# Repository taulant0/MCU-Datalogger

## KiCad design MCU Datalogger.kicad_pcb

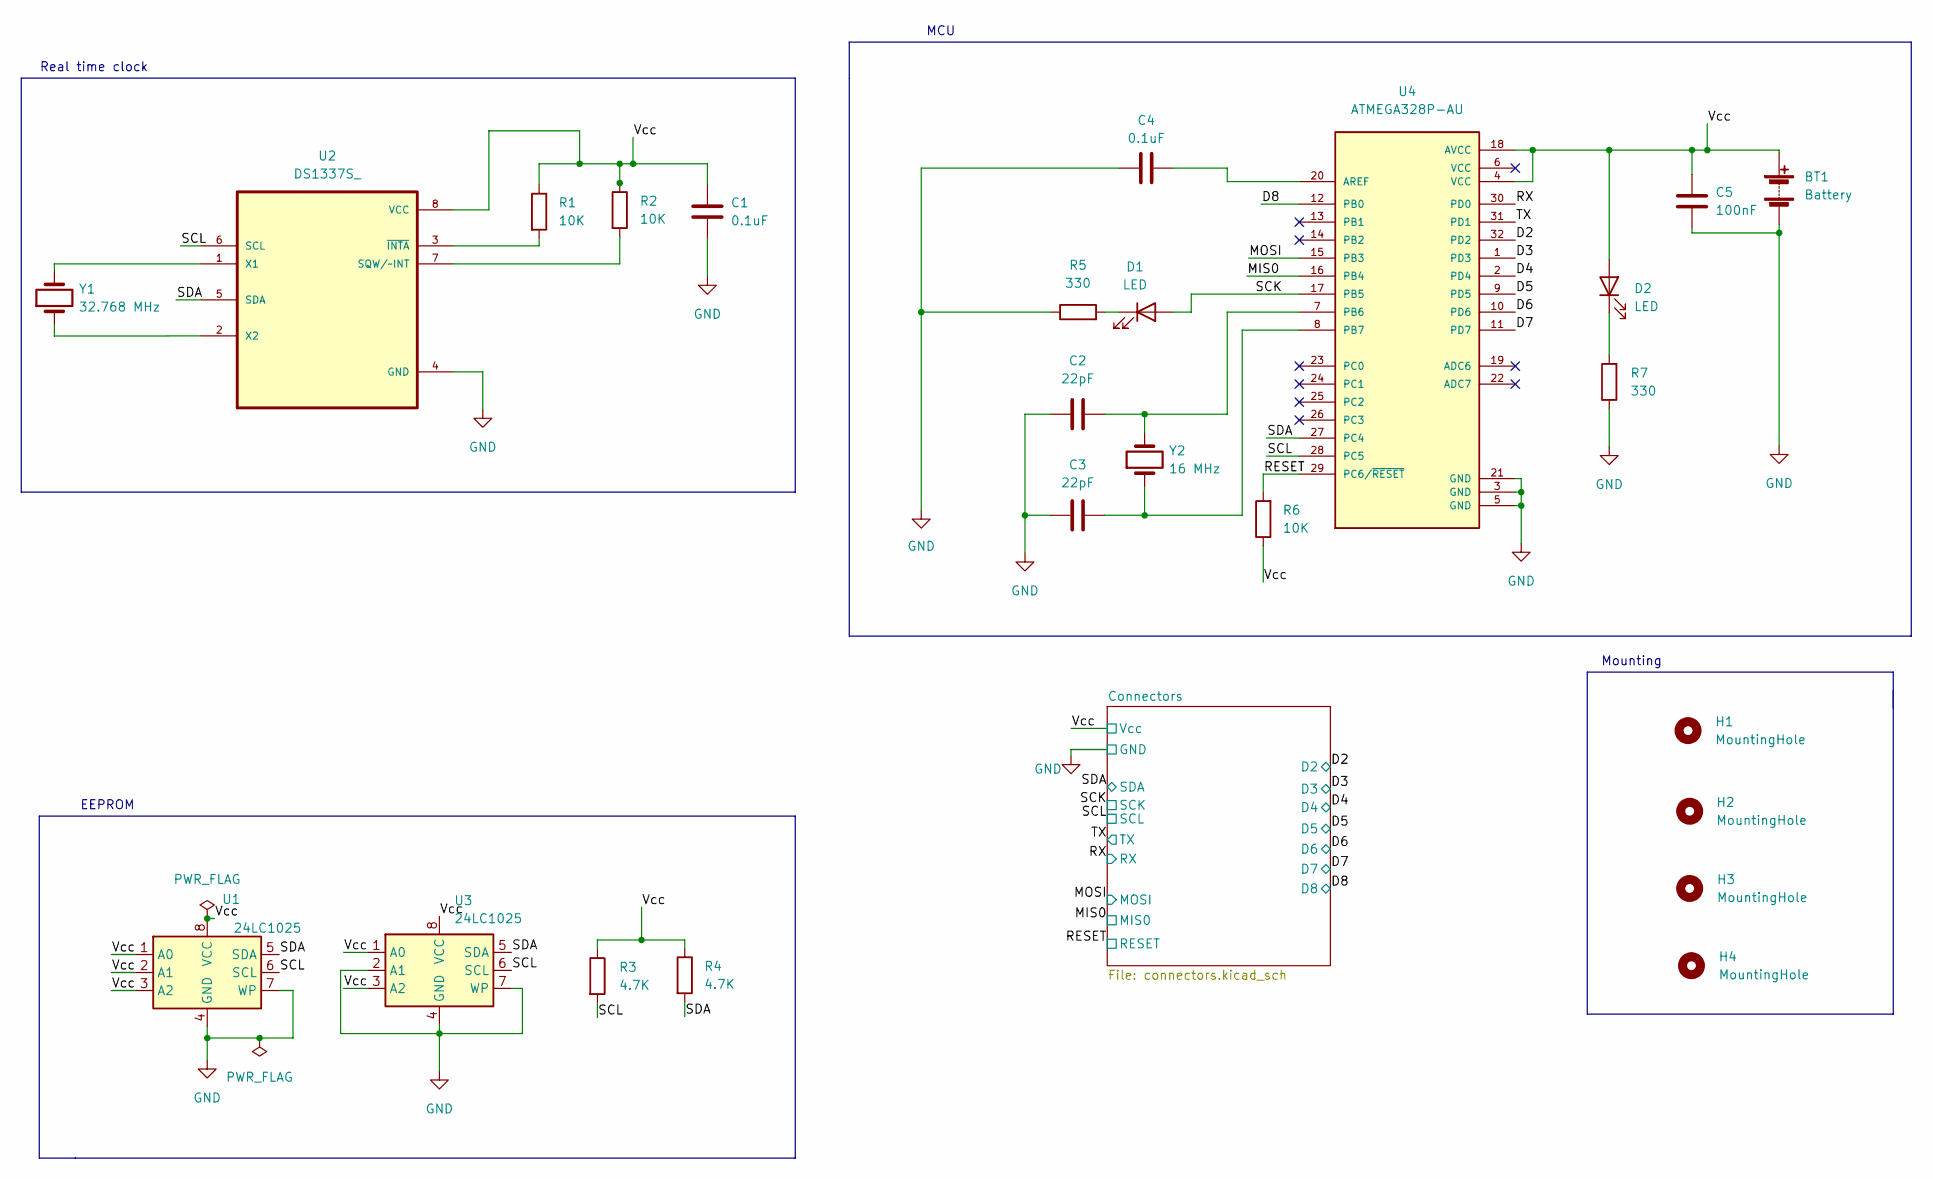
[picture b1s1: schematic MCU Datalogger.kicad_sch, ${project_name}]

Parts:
BT1: Battery; PinHeader_1x02_P2.54mm_Vertical
C1, C4: 0.1uF; C_0805_2012Metric
C2, C3: 22pF; C_0805_2012Metric
C5: 100nF; C_0805_2012Metric
D1, D2: LED; LED_0805_2012Metric
H1, H2, H3, H4: MountingHole; MountingHole_2.1mm
R1, R2, R6: 10K; R_0805_2012Metric
R3, R4: 4.7K; R_0805_2012Metric
R5, R7: 330; R_0805_2012Metric
U1, U3: 24LC1025; SOIC-8_5.23x5.23mm_P1.27mm
U2: DS1337S_; SOIC127P600X175-8N
U4: ATMEGA328P-AU; QFP80P900X900X120-32N; PARTREV 8271A
Y1: 32.768 MHz; Crystal_SMD_5032-2Pin_5.0x3.2mm_HandSoldering
Y2: 16 MHz; Crystal_SMD_5032-2Pin_5.0x3.2mm_HandSoldering

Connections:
/D2: U4.32 (PD2); also elsewhere on the board
/D3: U4.1 (PD3); also elsewhere on the board
/D4: U4.2 (PD4); also elsewhere on the board
/D5: U4.9 (PD5); also elsewhere on the board
/D6: U4.10 (PD6); also elsewhere on the board
/D7: U4.11 (PD7); also elsewhere on the board
/D8: U4.12 (PB0); also elsewhere on the board
/MIS0: U4.16 (PB4); also elsewhere on the board
/MOSI: U4.15 (PB3); also elsewhere on the board
/RESET: R6.2, U4.29 (PC6/~RESET); also elsewhere on the board
/RX: U4.30 (PD0); also elsewhere on the board
/SCK: D1.2 (A), R3.2, U1.6 (SCL), U2.6 (SCL), U3.6 (SCL), U4.17 (PB5), U4.28 (PC5); also elsewhere on the board
/SDA: R4.2, U1.5 (SDA), U2.5 (SDA), U3.5 (SDA), U4.27 (PC4); also elsewhere on the board
/TX: U4.31 (PD1); also elsewhere on the board
/Vcc: BT1.1 (+), C1.1, C5.1, D2.2 (A), R1.1, R2.1, R3.1, R4.1, R6.1, U1.1 (A0), U1.2 (A1), U1.3 (A2), U1.8 (VCC), U2.8 (VCC), U3.1 (A0), U3.3 (A2), U3.8 (VCC), U4.4 (VCC), U4.18 (AVCC); also elsewhere on the board
GND: BT1.2 (-), C1.2, C2.2, C3.1, C4.1, C5.2, R5.1, R7.1, U1.4 (GND), U1.7 (WP), U2.4 (GND), U3.2 (A1), U3.4 (GND), U3.7 (WP), U4.3 (GND), U4.5 (GND), U4.21 (GND); also elsewhere on the board
unnamed: C2.1, U4.7 (PB6), Y2.2
unnamed: C3.2, U4.8 (PB7), Y2.1
unnamed: C4.2, U4.20 (AREF)
unnamed: D1.1 (K), R5.2
unnamed: D2.1 (K), R7.2
unnamed: R1.2, U2.3 (~INTA)
unnamed: R2.2, U2.7 (SQW/~INT)
unnamed: U2.1 (X1), Y1.2
unnamed: U2.2 (X2), Y1.1

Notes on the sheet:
EEPROM
Real time clock
Mounting
MCU

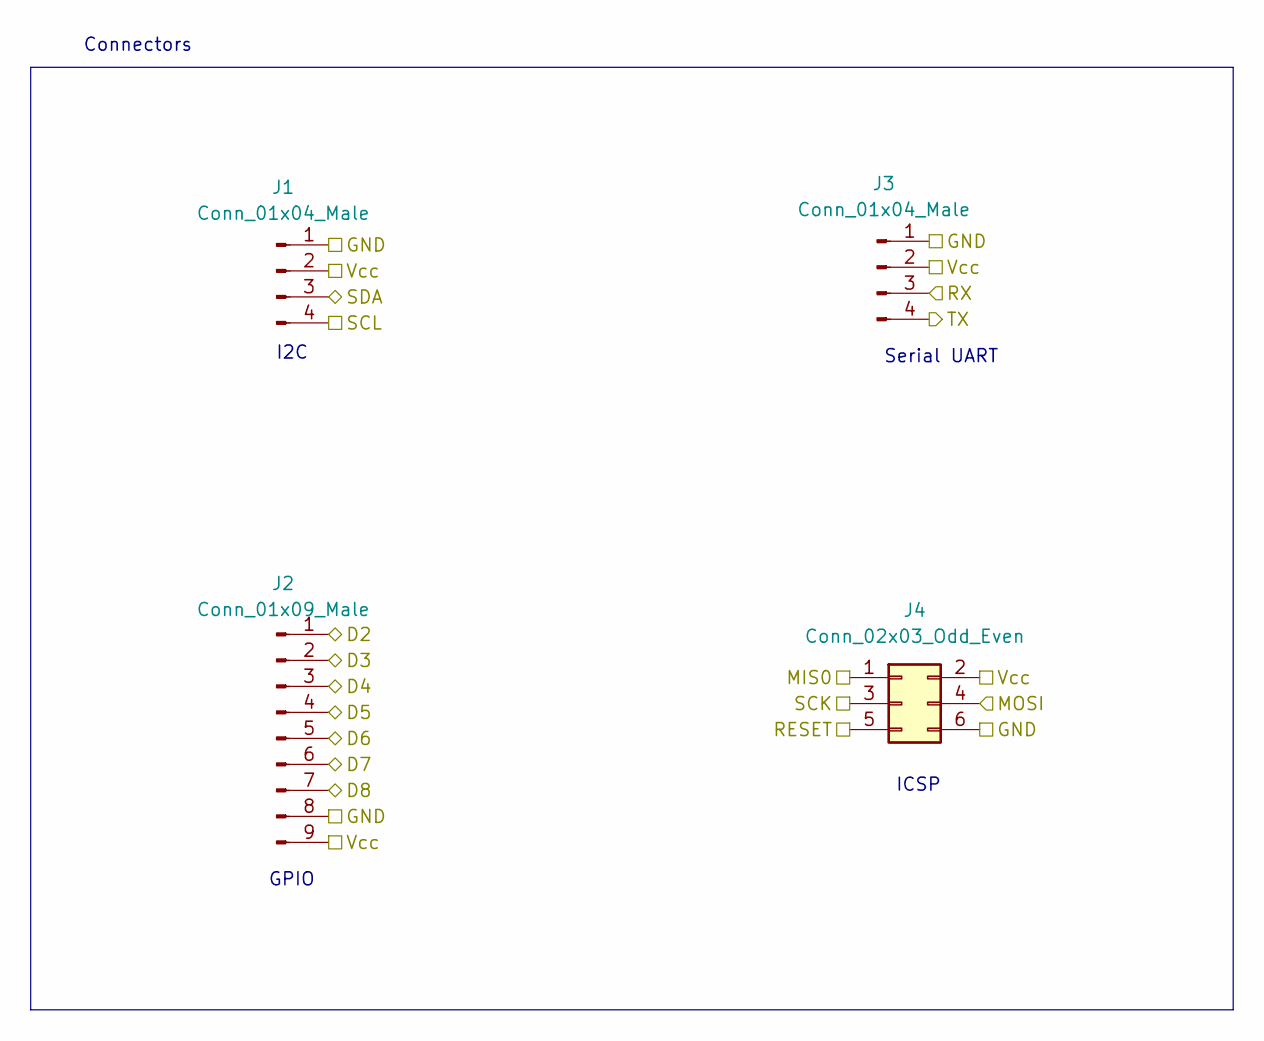
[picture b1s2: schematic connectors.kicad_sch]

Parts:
J1, J3: Conn_01x04_Male; PinHeader_1x04_P2.54mm_Vertical
J2: Conn_01x09_Male; PinHeader_1x09_P2.54mm_Vertical
J4: Conn_02x03_Odd_Even; PinHeader_2x03_P2.54mm_Vertical

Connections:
/D2: J2.1; also elsewhere on the board
/D3: J2.2; also elsewhere on the board
/D4: J2.3; also elsewhere on the board
/D5: J2.4; also elsewhere on the board
/D6: J2.5; also elsewhere on the board
/D7: J2.6; also elsewhere on the board
/D8: J2.7; also elsewhere on the board
/MIS0: J4.1; also elsewhere on the board
/MOSI: J4.4; also elsewhere on the board
/RESET: J4.5; also elsewhere on the board
/RX: J3.3; also elsewhere on the board
/SCK: J1.4, J4.3; also elsewhere on the board
/SDA: J1.3; also elsewhere on the board
/TX: J3.4; also elsewhere on the board
/Vcc: J1.2, J2.9, J3.2, J4.2; also elsewhere on the board
GND: J1.1, J2.8, J3.1, J4.6; also elsewhere on the board

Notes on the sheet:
I2C
GPIO
Serial UART
ICSP
Connectors

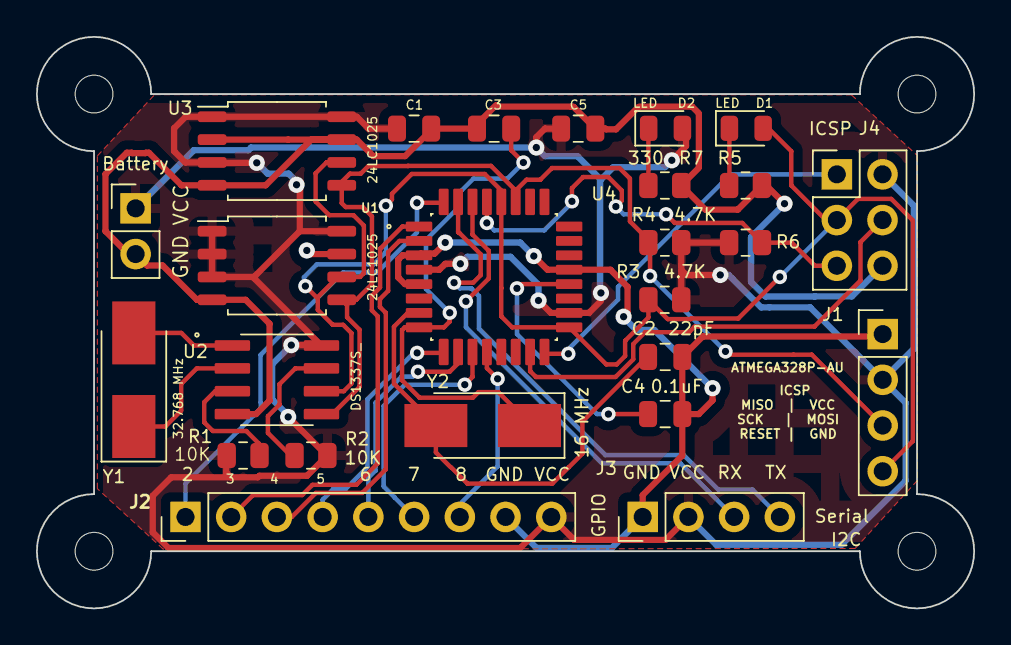
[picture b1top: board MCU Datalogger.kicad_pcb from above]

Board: 2 copper layers, 52.1 x 31.7 mm, 29 parts (0 on the bottom side), 25 nets.

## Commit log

2025-05-22 First commit of new project.
2025-05-22 Setup of EEschema for new project.
2025-05-22 Have added required symbols to the schematic sheets.
2025-05-22 Changed locations of symbols (arrange).
2025-05-22 Added component values.
2025-05-22 Completed symbol-footprint associations.
2025-05-22 Completed wiring of main sheet.
2025-05-22 Allocated GND and Vcc nets to the Power net
2025-05-22 Completed comments.
2025-05-22 Setup Pcbnew.
2025-05-22 Completed placement of footprints.
2025-05-22 Refined and completed outline
2025-05-22 Routing sans GND Vcc complete.
2025-05-23 Completed routing.
2025-05-23 Fixed outstanding issues.
2025-05-23 Completed 2-layer PCB project.
2025-05-23 Completed 2-layer PCB.
2025-05-23 Completed 4-layer pcb routing.
2025-05-23 Fixed two defects in the schematic.
2025-05-23 Added gitattributes file to prevent PCB Files from merge
2025-05-24 Fixed net bugs in 4 layer version of the PCB.
2025-05-24 Done
2025-05-24 Added 3d models for Y1 and Y2
2025-05-25 Added downloadble files.
